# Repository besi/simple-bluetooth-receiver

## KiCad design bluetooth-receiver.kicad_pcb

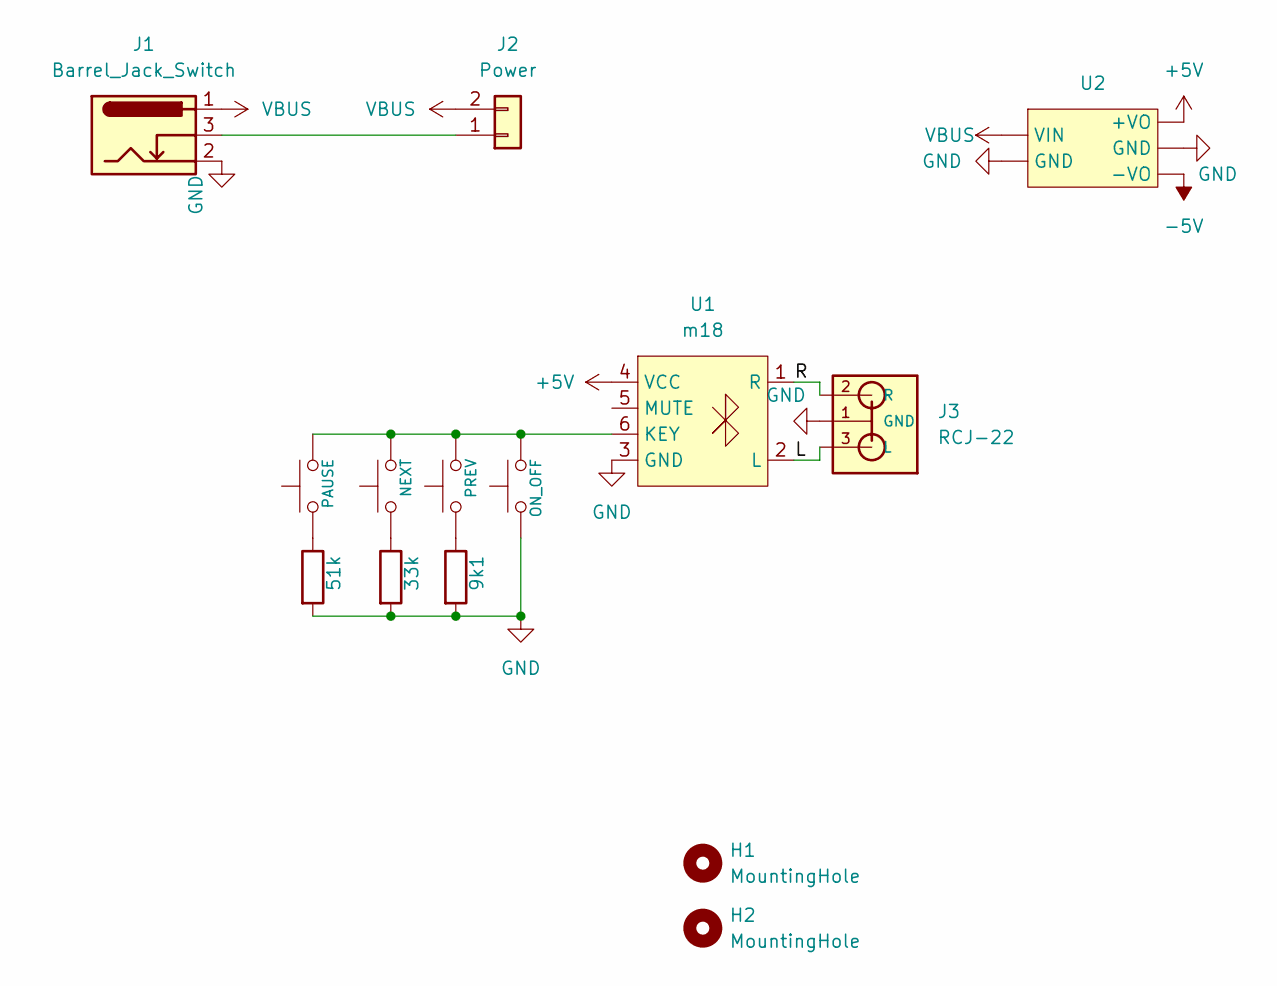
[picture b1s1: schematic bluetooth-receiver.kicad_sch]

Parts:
H1, H2: MountingHole; MountingHole_3.2mm_M3
J1: Barrel_Jack_Switch; BarrelJack_GCT_DCJ200-10-A_Horizontal
J2: Power; PinHeader_1x02_P2.54mm_Vertical
J3: RCJ-22; rcj-22
R1: 51k; R_Axial_DIN0411_L9.9mm_D3.6mm_P5.08mm_Vertical
R2: 33k; R_Axial_DIN0411_L9.9mm_D3.6mm_P5.08mm_Vertical
R3: 9k1; R_Axial_DIN0411_L9.9mm_D3.6mm_P5.08mm_Vertical
SW1: PAUSE; pts636
SW2: NEXT; pts636
SW3: PREV; pts636
SW4: ON_OFF; pts636
U1: m18
U2: dd1718pa

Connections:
+5V: U1.4 (VCC), U2.3 (+VO)
-5V: U2.5 (-VO)
/L: J3.3 (L), U1.2 (L)
/R: J3.2 (R), U1.1 (R)
GND: J1.2, J3.1 (GND), R1.2, R2.2, R3.2, SW4.1, U1.3 (GND), U2.2 (GND), U2.4 (GND)
unnamed: J1.3, J2.1
unnamed: R1.1, SW1.1
unnamed: R2.1, SW2.1
unnamed: R3.1, SW3.1
unnamed: SW1.2, SW2.2, SW3.2, SW4.2, U1.6 (KEY)
VBUS: J1.1, J2.2, U2.1 (VIN)

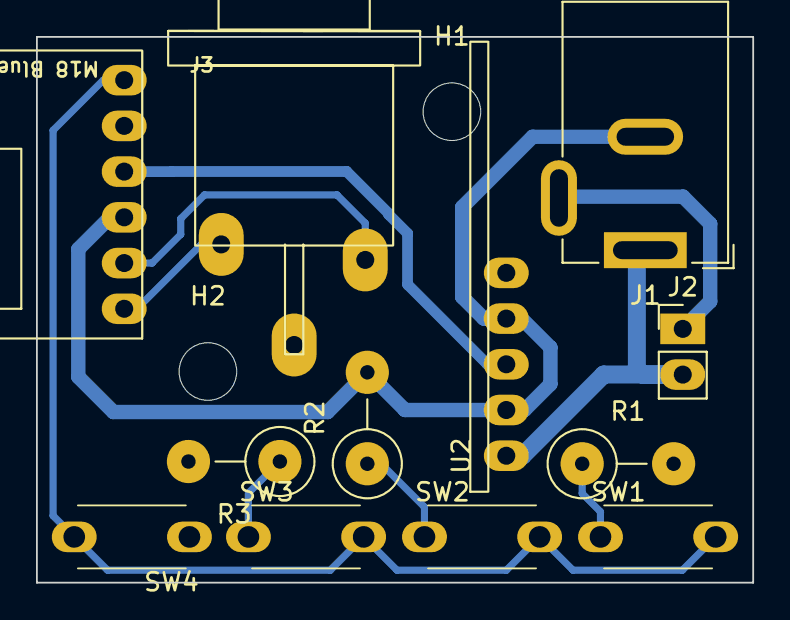
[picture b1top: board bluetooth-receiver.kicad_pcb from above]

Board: 2 copper layers, 39.8 x 30.3 mm, 14 parts (0 on the bottom side), 10 nets.

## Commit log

2024-01-27 Initial pcb
2024-01-31 Update bluetooth receiver
2024-05-31 Prepare for milling
2024-05-31 Add mounting holes
2024-05-31 Ignore plots
